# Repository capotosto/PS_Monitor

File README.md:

# Multi-Rail Isolated Power Supply Monitoring System

**Repository:** `PS_Monitor`  
**Author:** Mike Capotosto

## Project Overview

The Multi-Rail Isolated Power Supply Monitoring System measures the voltage and current of up to six floating power-supply rails while preserving galvanic isolation between measurement channels. Each rail is monitored by an LTC2945 power monitor connected through an isolated I²C interface to an Arduino GIGA R1 WiFi. The Arduino firmware performs data acquisition, engineering-unit conversion, alarm evaluation, persistent configuration storage, local display control, HTTP service, and Ethernet communication with an EPICS Input/Output Controller. Measurement and status information is presented locally on the GIGA Display Shield, through a browser-based dashboard, and remotely through a Phoebus Control System Studio operator interface.

The monitored rails are:

- `+5VA`
- `+5VB`
- `+5V`
- `-5V`
- `+15V`
- `-15V`

---

## System Features

- Six isolated voltage and current measurement channels
- LTC2945 voltage, current, and power monitoring
- Independent I²C isolation for each floating rail
- Support for positive and negative supply rails
- Configurable upper and lower voltage limits
- Configurable upper and lower current limits
- Persistent alarm and network settings stored in internal QSPI flash
- Local touchscreen display using the Arduino GIGA Display Shield
- Browser-based monitoring and configuration dashboard
- Ethernet communication through the Arduino Ethernet Shield
- PSC (Portable Streaming Controller) protocol interface for EPICS integration
- EPICS Process Variables for measurements, limits, alarms, and status
- Phoebus OPI for centralized operator monitoring
- I²C communication-error detection
- Text-based alarm states such as `OVL`, `UVL` (over/under voltage limit), `OCL`, and `UCL` (over/under current limit)

---

## System Architecture

### Data Flow

```text
┌──────────────────────────────────────────────┐
│ Floating Power-Supply Rails                  │
│ +5VA, +5VB, +5V, -5V, +15V, and -15V        │
└──────────────────────┬───────────────────────┘
                       │
                       ▼
┌──────────────────────────────────────────────┐
│ LTC2945 Voltage and Current Monitors         │
│ One monitor per power-supply rail            │
└──────────────────────┬───────────────────────┘
                       │
                       ▼
┌──────────────────────────────────────────────┐
│ Isolated I²C Interfaces                      │
│ Maintains isolation between floating rails   │
└──────────────────────┬───────────────────────┘
                       │
                       ▼
┌──────────────────────────────────────────────┐
│ Arduino GIGA R1 WiFi Firmware                │
│                                              │
│ • Sensor acquisition                         │
│ • Engineering-unit conversion                │
│ • Negative-rail sign correction              │
│ • Alarm evaluation                           │
│ • Persistent settings                        │
│ • Local display                              │
│ • HTTP dashboard                             │
│ • PSC protocol server                        │
└───────────────┬────────────────────┬─────────┘
                │                    │
                ▼                    ▼
┌─────────────────────────┐  ┌──────────────────────┐
│ GIGA Display Shield     │  │ Ethernet Network     │
│ Local touchscreen UI    │  │ HTTP and PSC         │
└─────────────────────────┘  └──────────┬───────────┘
                                       │
                                       ▼
                            ┌────────────────────────┐
                            │ EPICS IOC              │
                            │ PSCDriver and records  │
                            └──────────┬─────────────┘
                                       │
                                       ▼
                            ┌────────────────────────┐
                            │ Phoebus / CSS OPI      │
                            │ Operator interface     │
                            └────────────────────────┘
```

### Major Subsystems

| Subsystem | Function |
|---|---|
| Sensor hardware | Measures rail voltage, shunt voltage, current, and power |
| I²C isolation | Preserves galvanic isolation between floating rails |
| Arduino firmware | Acquires data, evaluates alarms, stores settings, and manages communications |
| Local display | Shows rail measurements, limits, alarms, and communication status |
| HTTP dashboard | Provides browser-based monitoring and configuration |
| PSC interface | Transfers measurement and status data to the EPICS IOC |
| EPICS IOC | Converts device data into EPICS Process Variables |
| Phoebus OPI | Provides the centralized operator interface |

---

## Repository Structure

```text
PS_Monitor/
├── README.md
├── hardware/
│   ├── kicad/
│   ├── bom/
│   ├── gerbers/
│   ├── mechanical/
│   └── datasheets/
├── firmware/
│   ├── platformio.ini
│   ├── include/
│   ├── lib/
│   ├── src/
│   └── test/
├── epics-ioc/
│   ├── configure/
│   ├── db/
│   ├── dbd/
│   ├── iocBoot/
│   ├── psuMonitorApp/
│   └── opi/
└── documentation/
```

### Directory Descriptions

- **`/hardware`**  
  KiCad schematic and PCB files, manufacturing outputs, bill of materials, mechanical drawings, and related.

- **`/firmware`**  
  PlatformIO project for the Arduino GIGA R1 WiFi. This directory contains the application source code, configuration headers, local libraries, and build configuration.

- **`/epics-ioc`**  
  EPICS IOC source tree containing database files, record definitions, startup scripts, PSCDriver configuration, device communication settings, and Phoebus Control System Studio displays.

- **`/documentation`**  
  Assorted Documentation

---

## Hardware

### Primary Components

- Arduino GIGA R1 WiFi
- Arduino GIGA Display Shield
- Arduino Ethernet Shield
- LTC2945 voltage, current, and power monitors
- DC1697A LTC2945 demonstration board for prototype testing
- Per-channel I²C digital isolators
- Current-sense shunt resistors
- Custom monitoring and interface PCB
- Six isolated power-supply inputs

### Measurement Method

Each LTC2945 measures:

- Supply voltage
- Differential voltage across a current-sense shunt
- Calculated load current
- Calculated electrical power

Because each monitored supply may float at a different potential, every sensor channel communicates through its own isolated I²C interface. Negative rails are monitored within their isolated domains, and the firmware applies the appropriate sign to the reported engineering values.

---

## Firmware

The firmware is built with PlatformIO using the Arduino Mbed OS framework.

### Main Firmware Modules

| Module | Responsibility |
|---|---|
| `AppState` | Global channel data, settings, alarms, and system state |
| `SensorManager` | Sensor initialization, acquisition, and channel updates |
| `LTC2945` | Low-level LTC2945 register access and unit conversion |
| `DisplayUI` | GIGA Display Shield rendering and status updates |
| `EthernetServices` | Ethernet initialization and network service handling |
| `HttpDashboard` | Browser-based monitoring and configuration |
| `PscProtocol` | PSC protocol communication with the EPICS IOC |
| `PersistentStorage` | QSPI storage of alarm limits and network settings |
| `main` | System initialization and application scheduling |

### Firmware Configuration

Hardware-specific settings are stored in configuration headers, including:

- I²C addresses
- Shunt-resistance values
- Channel names
- Rail polarity
- Voltage and current scaling
- Default alarm limits
- Static network configuration
- MAC address
- PSC port configuration
- Sensor polling intervals

---

## Persistent Settings

The firmware stores configuration data in the Arduino GIGA internal QSPI flash using LittleFS.

Saved settings include:

- Per-channel voltage-low limit
- Per-channel voltage-high limit
- Per-channel current-low limit
- Per-channel current-high limit
- Static IP address
- Subnet mask
- Gateway address
- DNS server address
---

## Network Interfaces

### HTTP Dashboard

The firmware hosts a local web interface for:

- Viewing voltage and current measurements
- Viewing alarm and communication status
- Editing alarm limits
- Editing network parameters
- Saving settings to QSPI

### PSC Protocol

The Arduino exposes a PSC protocol service over Ethernet. The EPICS IOC connects to the device using PSCDriver and maps transmitted parameters into EPICS records.

---

## EPICS IOC

### Requirements

- EPICS Base
- ASYN
- PSCDriver
- A supported Linux environment
- Phoebus for the operator interface

### Build the IOC

From the repository root:

```bash
cd epics-ioc
make
```

### Start the IOC

```bash
cd iocBoot/iocpsuMonitor
./st.cmd
```

An equivalent direct launch command may also be used:

```bash
../../bin/linux-x86_64/psuMonitor st.cmd
```

### Example IOC Configuration

```text
P=TEST:
R=GIGA
DEVICE=GIGA_PSC
HOST=192.168.1.177
PORT=8765
```

The final values are defined in the IOC startup script.

---

## EPICS Process Variables

The IOC is intended to provide Process Variables for:

- Channel voltage
- Channel current
- Voltage-low limit
- Voltage-high limit
- Current-low limit
- Current-high limit
- Voltage alarm status
- Current alarm status
- Sensor communication status
- I²C error status
- Arduino connection status
- Network information
- Firmware status

### Alarm States

| Status | Meaning |
|---|---|
| `OK` | Measurement is within configured limits |
| `OVL` | Over-voltage limit |
| `UVL` | Under-voltage limit |
| `OCL` | Over-current limit |
| `UCL` | Under-current limit |
| `I2C Error` | Sensor communication failure |
| `Disconnected` | IOC communication failure |

---

## Operator Interface

The Phoebus OPI provides a centralized display for all monitored rails.

Planned or implemented interface elements include:

- Voltage and current readbacks
- Alarm-limit displays
- Text-based alarm indicators
- Connection-status indicator
- I²C error indicator
- Per-channel status cards
- Network and firmware information
- Overall system status

---

## Project Milestones

- [x] Define system requirements and monitored power rails
- [x] Select the Arduino GIGA R1 WiFi as the primary controller
- [x] Establish the PlatformIO firmware project
- [x] Develop the initial six-channel display layout
- [x] Add configurable voltage and current alarm limits
- [x] Establish the Ethernet and PSC communication architecture
- [x] Complete single-channel LTC2945 prototype validation
- [ ] Verify current scaling for each shunt-resistor value
- [ ] Complete six-channel isolated I²C hardware
- [ ] Finalize persistent storage and recovery testing
- [ ] Complete browser-based configuration testing
- [ ] Finalize EPICS database records
- [ ] Complete Phoebus OPI
- [ ] Fabricate and assemble the custom PCB
- [ ] Calibrate all measurement channels
- [ ] Perform end-to-end system validation
- [ ] Complete final project documentation

---

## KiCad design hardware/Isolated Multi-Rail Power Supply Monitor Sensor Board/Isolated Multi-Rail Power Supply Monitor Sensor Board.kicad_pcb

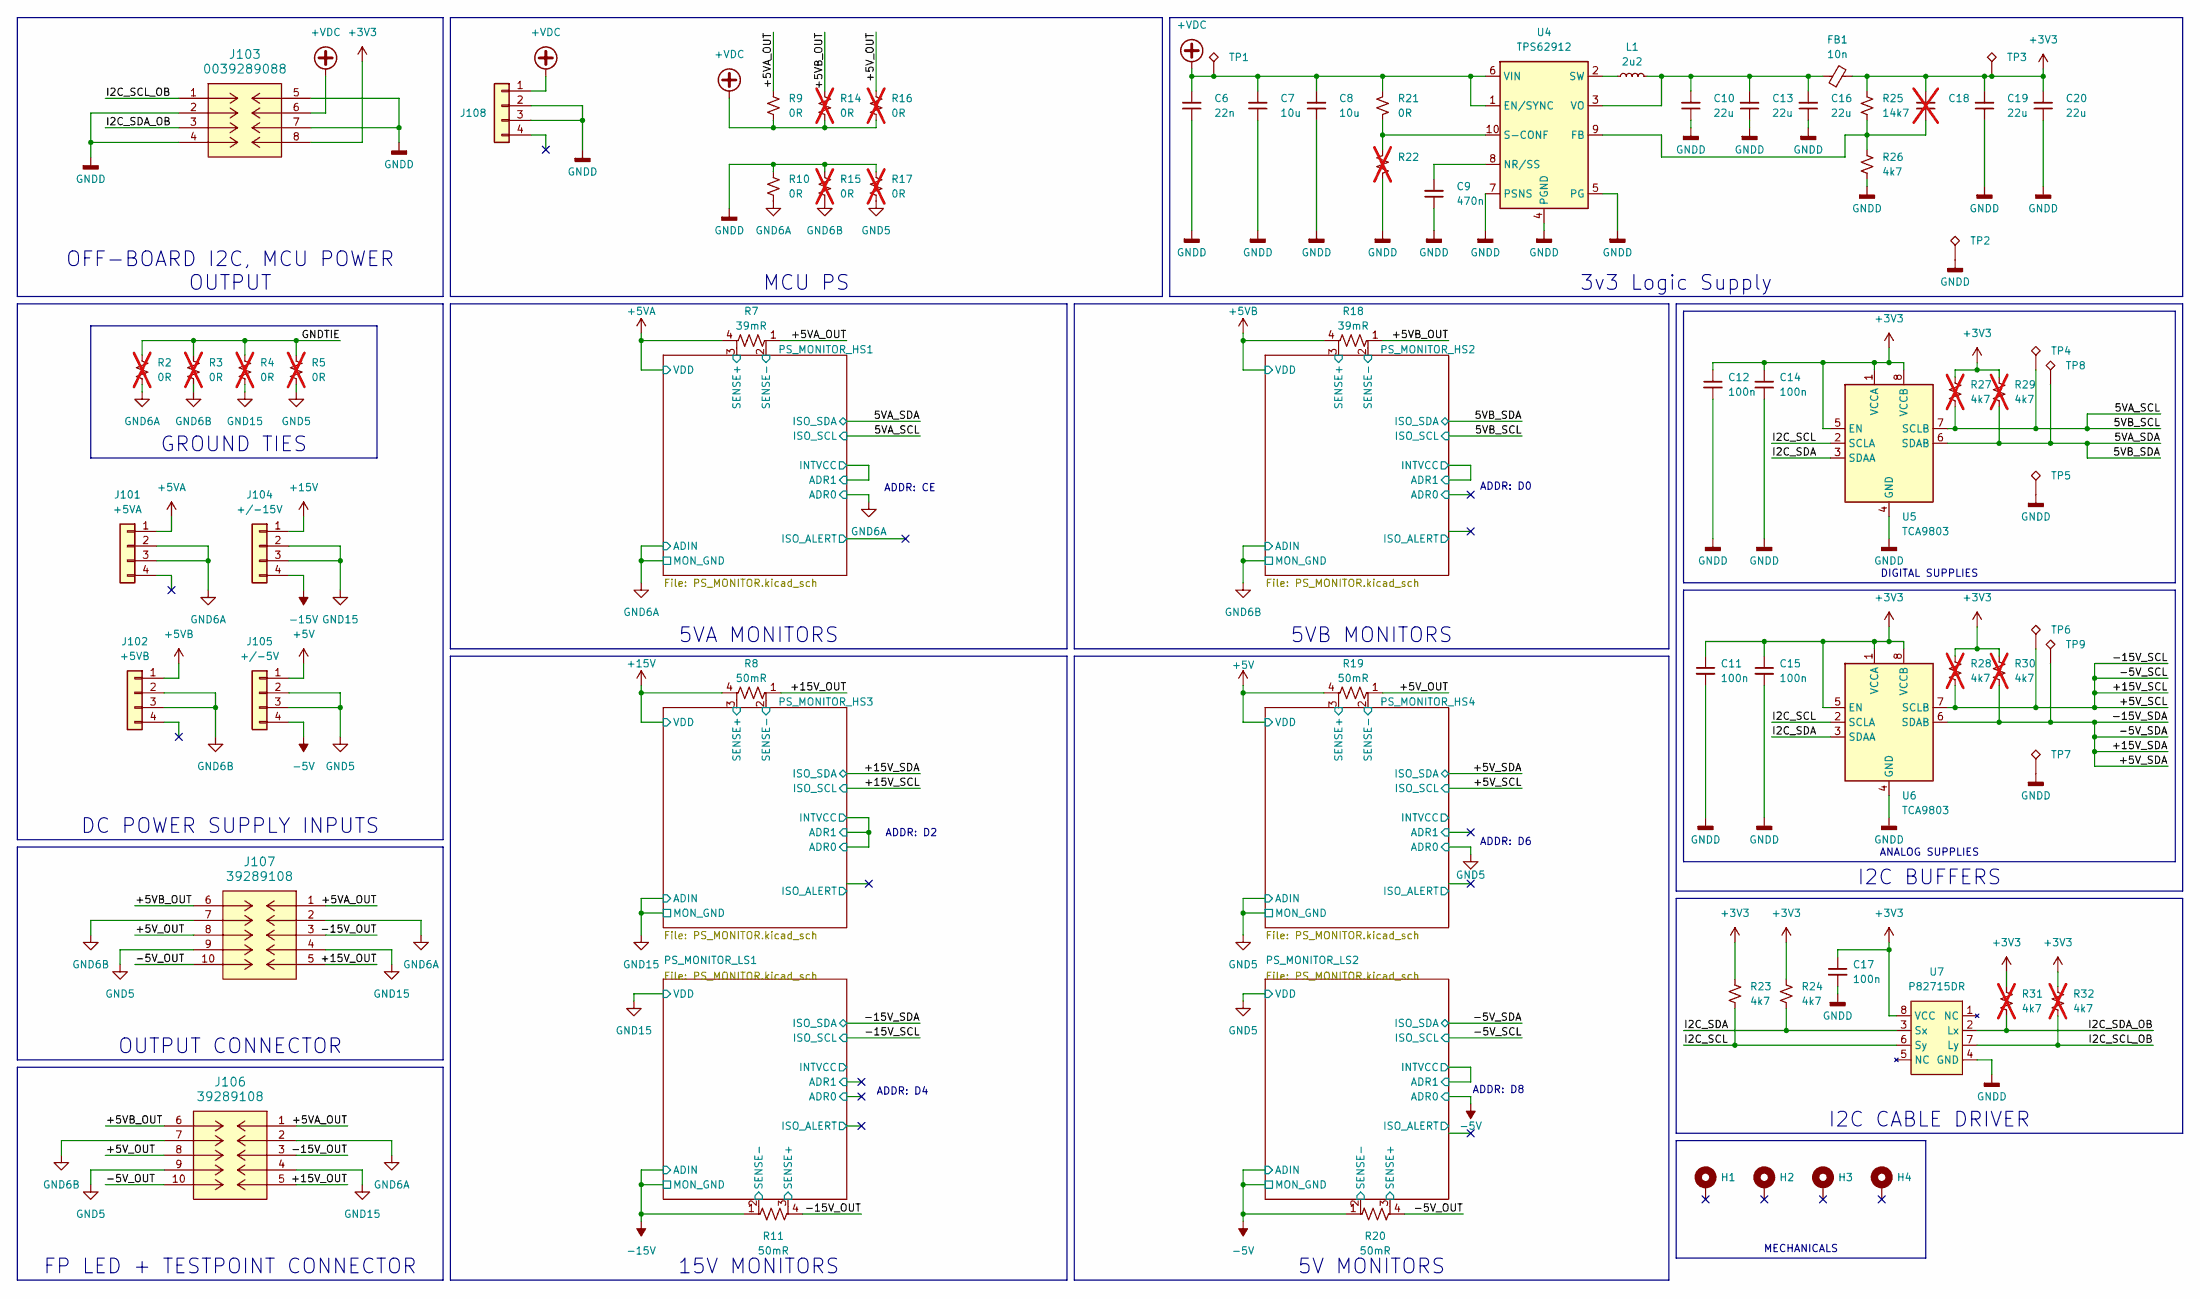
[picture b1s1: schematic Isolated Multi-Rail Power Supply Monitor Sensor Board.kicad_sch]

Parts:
C6: 22n; C_0402_1005Metric; MPN GRM155R71H222KA01D
C7, C8: 10u; C_0805_2012Metric; MPN C2012X7S1E106K125AC
C9: 470n; C_0402_1005Metric; MPN C1005X5R1E474K050BB
C10, C13, C16, C19, C20: 22u; C_0805_2012Metric; MPN GMC21X7S226M10NT
C11, C12, C14, C15, C17: 100n; C_0402_1005Metric; MPN GRM155R61H104KE14D
C18: C_0603_1608Metric; not fitted
FB1: 10n; L_0603_1608Metric; MPN BLE18PS080SN1D
H1, H2, H3, H4: MountingHole_Pad; MountingHole_3.2mm_M3_DIN965_Pad
J101: +5VA; Molex_Mini-Fit_Jr_5566-04A2_2x02_P4.20mm_Vertical; MPN 0039299049
J102: +5VB; Molex_Mini-Fit_Jr_5566-04A2_2x02_P4.20mm_Vertical; MPN 0039299049
J103: 0039289088; Molex_Mini-Fit_Jr_5566-08A2_2x04_P4.20mm_Vertical; MPN 0039289088
J104: +/-15V; Molex_Mini-Fit_Jr_5566-04A2_2x02_P4.20mm_Vertical; MPN 0039299049
J105: +/-5V; Molex_Mini-Fit_Jr_5566-04A2_2x02_P4.20mm_Vertical; MPN 0039299049
J106, J107: 39289108; Molex_Mini-Fit_Jr_5566-10A2_2x05_P4.20mm_Vertical; MPN 0039289108
J108: Conn_01x04; Molex_Mini-Fit_Jr_5566-04A2_2x02_P4.20mm_Vertical; MPN 0039299049
L1: 2u2; 74438356022; MPN 74438356022
R2, R3, R4, R5, R14, R15, R16, R17: 0R; R_1206_3216Metric; Tolerance JUMPER; MPN 5108; not fitted
R7, R18: 39mR; R_Shunt_Ohmite_LVK20; MPN LVK20R039FER
R8, R11, R19, R20: 50mR; R_Shunt_Ohmite_LVK20; MPN LVK20R050FER
R9, R10: 0R; R_1206_3216Metric; Tolerance JUMPER; MPN 5108
R21: 0R; R_0402_1005Metric; MPN CRCW04020000Z0ED
R22: R_0402_1005Metric; not fitted
R23, R24: 4k7; R_0402_1005Metric; MPN CRCW04024K70FKED
R25: 14k7; R_0402_1005Metric; MPN ERA-2APB1472X
R26: 4k7; R_0402_1005Metric; MPN ERA-2ARB472X
R27, R28, R29, R30, R31, R32: 4k7; R_0402_1005Metric; MPN CRCW04024K70FKED; not fitted
TP1, TP3: 5000; TestPoint_Keystone_5000-5004_Miniature; MPN 5000
TP2: 5001; TestPoint_Keystone_5000-5004_Miniature; MPN 5001
TP4, TP5, TP6, TP7, TP8, TP9: 5015; TestPoint_Keystone_5015_Micro_Mini; MPN 5015
U4: TPS62912; Texas_RPU0010A_VQFN-HR-10_2x2mm_P0.5mm; MPN TPS62912RPUR
U5, U6: TCA9803; VSSOP-8_3x3mm_P0.65mm; MPN TCA9803DGKR
U7: P82715DR; SOIC-8_3.9x4.9mm_P1.27mm; MPN P82B715DR

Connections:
+3V3: C11.1, C12.1, C14.1, C15.1, C17.1, C18.2, C19.2, C20.2, FB1.2, J103.8, R23.2, R24.2, R25.1, R27.2, R28.2, R29.2, R30.2, R31.2, R32.2, TP3.1, U5.1 (VCCA), U5.5 (EN), U5.8 (VCCB), U6.1 (VCCA), U6.5 (EN), U6.8 (VCCB), U7.8 (VCC); also elsewhere on the board
+5V: J105.1, R19.4; also elsewhere on the board
+6VA: J101.1, R7.4; also elsewhere on the board
+6VB: J102.1, R18.4; also elsewhere on the board
+15V: J104.1, R8.4; also elsewhere on the board
+VDC: C6.2, C7.2, C8.2, J103.6, J108.1, R9.2, R14.2, R16.2, R21.1, TP1.1, U4.1 (EN/SYNC), U4.6 (VIN)
-5V: J105.4, R20.1; also elsewhere on the board
-15V: J104.4, R11.1; also elsewhere on the board
/6VA_SCL: R27.1, TP4.1, U5.7 (SCLB); also elsewhere on the board
/6VA_SDA: R29.1, TP8.1, U5.6 (SDAB); also elsewhere on the board
/+5V_OUT: J106.8, J107.8, R16.1, R19.1
/+6VA_OUT: J106.1, J107.1, R7.1, R9.1
/+6VB_OUT: J106.6, J107.6, R14.1, R18.1
/+15V_OUT: J106.5, J107.5, R8.1
/+15V_SCL: R28.1, TP6.1, U6.7 (SCLB); also elsewhere on the board
/+15V_SDA: R30.1, TP9.1, U6.6 (SDAB); also elsewhere on the board
/-5V_OUT: J106.10, J107.10, R20.4
/-15V_OUT: J106.3, J107.3, R11.4
/GNDTIE: R2.1, R3.1, R4.1, R5.1
/I2C_SCL: R23.1, U5.2 (SCLA), U6.2 (SCLA), U7.6 (Sy)
/I2C_SCL_OB: J103.1, R32.1, U7.7 (Ly)
/I2C_SDA: R24.1, U5.3 (SDAA), U6.3 (SDAA), U7.3 (Sx)
/I2C_SDA_OB: J103.3, R31.1, U7.2 (Lx)
/PS_MONITOR_HS1/SENSE+: R7.3; also elsewhere on the board
/PS_MONITOR_HS1/SENSE-: R7.2; also elsewhere on the board
/PS_MONITOR_HS2/SENSE+: R18.3; also elsewhere on the board
/PS_MONITOR_HS2/SENSE-: R18.2; also elsewhere on the board
/PS_MONITOR_HS3/SENSE+: R8.3; also elsewhere on the board
/PS_MONITOR_HS3/SENSE-: R8.2; also elsewhere on the board
/PS_MONITOR_HS4/SENSE+: R19.3; also elsewhere on the board
/PS_MONITOR_HS4/SENSE-: R19.2; also elsewhere on the board
/PS_MONITOR_LS1/SENSE+: R11.3; also elsewhere on the board
/PS_MONITOR_LS1/SENSE-: R11.2; also elsewhere on the board
/PS_MONITOR_LS2/SENSE+: R20.3; also elsewhere on the board
/PS_MONITOR_LS2/SENSE-: R20.2; also elsewhere on the board
GND5: J105.2, J105.3, J106.9, J107.9, R5.2, R17.2; also elsewhere on the board
GND6A: J101.2, J101.3, J106.2, J107.2, R2.2, R10.2; also elsewhere on the board
GND6B: J102.2, J102.3, J106.7, J107.7, R3.2, R15.2; also elsewhere on the board
GND15: J104.2, J104.3, J106.4, J107.4, R4.2; also elsewhere on the board
GNDD: C6.1, C7.1, C8.1, C9.1, C10.1, C11.2, C12.2, C13.1, C14.2, C15.2, C16.1, C17.2, C19.1, C20.1, J103.2, J103.4, J103.5, J103.7, J108.2, J108.3, R10.1, R15.1, R17.1, R22.2, R26.2, TP2.1, TP5.1, TP7.1, U4.4 (PGND), U4.5 (PG), U4.7 (PSNS), U5.4 (GND), U6.4 (GND), U7.4 (GND); also elsewhere on the board
unnamed: C18.1, R25.2, R26.1, U4.9 (FB)
unnamed: C9.2, U4.8 (NR/SS)
unnamed: R21.2, R22.1, U4.10 (S-CONF)
unnamed: L1.1, U4.2 (SW)
unnamed: C10.2, C13.2, C16.2, FB1.1, L1.2, U4.3 (VO)

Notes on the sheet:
ADDR: D0
ADDR: D6
ADDR: D2
ADDR: D4
ADDR: D8
ADDR: CE
I2C BUFFERS
ANALOG SUPPLIES
5V MONITORS
5VA MONITORS
OFF-BOARD I2C, MCU POWER OUTPUT
3v3 Logic Supply
GROUND TIES
I2C CABLE DRIVER
5VB MONITORS
15V MONITORS
MECHANICALS
FP LED + TESTPOINT CONNECTOR
OUTPUT CONNECTOR
MCU PS
DC POWER SUPPLY INPUTS
DIGITAL SUPPLIES

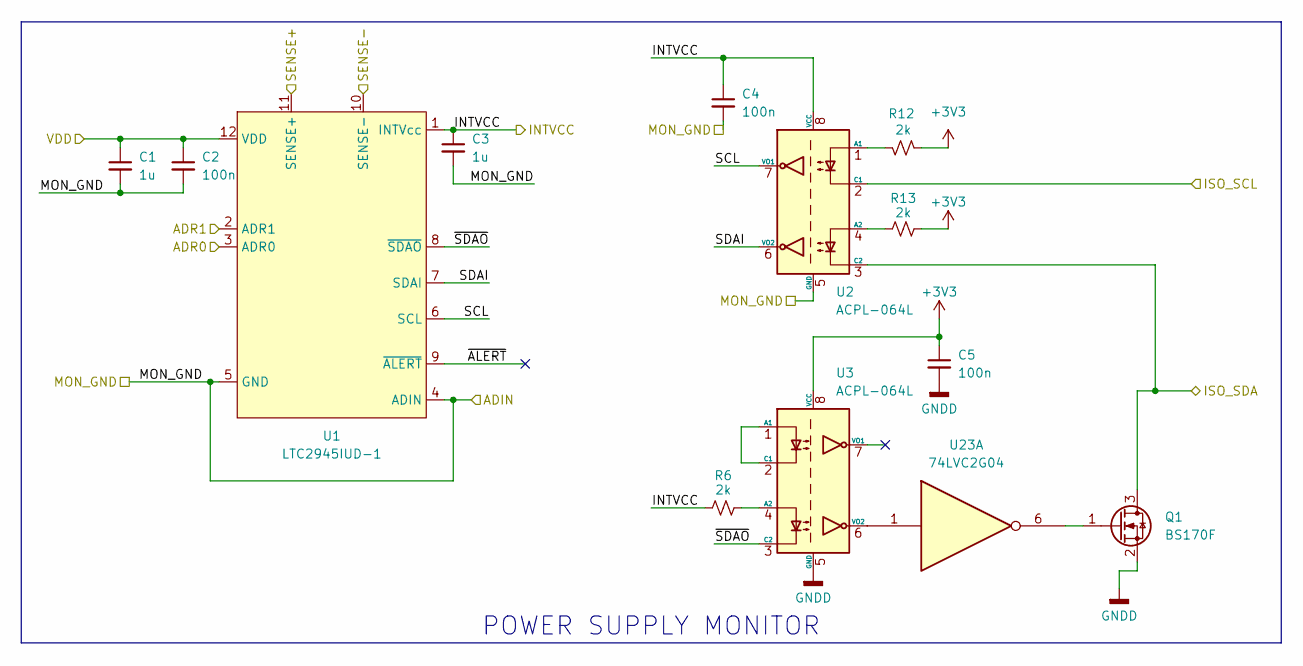
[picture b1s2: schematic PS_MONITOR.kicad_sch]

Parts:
C1, C3: 1u; C_0603_1608Metric; MPN CL10A105KB8NNNC
C2, C4, C5: 100n; C_0402_1005Metric; MPN GRM155R61H104KE14D
Q1: BS170F; SOT-416; MPN NTA7002NT1G
R6, R12, R13: 2k; R_0402_1005Metric; MPN ERJ-2RKF2001X
U1: LTC2945IUD-1; QFN-12-1EP_3x3mm_P0.5mm_EP1.65x1.65mm_ThermalVias; MPN LTC2945IUD#TRPBF
U2, U3: ACPL-064L; SOIC-8_3.9x4.9mm_P1.27mm; MPN ACPL-064L-500E
U23: 74LVC2G04

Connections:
+3V3: C5.1, R12.1, R13.2, U3.8 (VCC); also elsewhere on the board
+6VA: C1.1, C2.1, U1.12 (VDD); also elsewhere on the board
/6VA_SCL: U2.2 (C1); also elsewhere on the board
/6VA_SDA: Q1.3 (D), U2.3 (C2); also elsewhere on the board
/PS_MONITOR_HS1/INTVCC: C3.1, C4.1, R6.1, U1.1 (INTVcc), U1.2 (ADR1), U2.8 (VCC)
/PS_MONITOR_HS1/SCL: U1.6 (SCL), U2.7 (VO1)
/PS_MONITOR_HS1/SDAI: U1.7 (SDAI), U2.6 (VO2)
/PS_MONITOR_HS1/SENSE+: U1.11 (SENSE+); also elsewhere on the board
/PS_MONITOR_HS1/SENSE-: U1.10 (SENSE-); also elsewhere on the board
/PS_MONITOR_HS1/~ALERT: U1.9 (~ALERT)
/PS_MONITOR_HS1/~SDAO: U1.8 (~SDAO), U3.3 (C2)
GND6A: C1.2, C2.2, C3.2, C4.2, U1.3 (ADR0), U1.4 (ADIN), U1.5 (GND), U1.13 (GND), U2.5 (GND); also elsewhere on the board
GNDD: C5.2, Q1.2 (S), U3.5 (GND); also elsewhere on the board
unnamed: Q1.1 (G), U3.6 (VO2)
unnamed: R12.2, U2.1 (A1)
unnamed: R13.1, U2.4 (A2)
unnamed: U3.1 (A1), U3.2 (C1)
unnamed: R6.2, U3.4 (A2)

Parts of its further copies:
C21, C23, C26, C28, C31, C33, C36, C38, C41, C43: 1u; C_0603_1608Metric; MPN CL10A105KB8NNNC
C22, C24, C25, C27, C29, C30, C32, C34, C35, C37, C39, C40, C42, C44, C45: 100n; C_0402_1005Metric; MPN GRM155R61H104KE14D
Q2, Q3, Q4, Q5, Q6: BS170F; SOT-416; MPN NTA7002NT1G
R33, R34, R35, R36, R37, R38, R39, R40, R41, R42, R43, R44, R45, R46, R47: 2k; R_0402_1005Metric; MPN ERJ-2RKF2001X
U8, U11, U14, U17, U20: LTC2945IUD-1; QFN-12-1EP_3x3mm_P0.5mm_EP1.65x1.65mm_ThermalVias; MPN LTC2945IUD#TRPBF
U9, U10, U12, U13, U15, U16, U18, U19, U21, U22: ACPL-064L; SOIC-8_3.9x4.9mm_P1.27mm; MPN ACPL-064L-500E

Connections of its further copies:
+3V3: C25.1, C30.1, C35.1, C40.1, C45.1, R34.1, R35.2, R37.1, R38.2, R40.1, R41.2, R43.1, R44.2, R46.1, R47.2, U10.8 (VCC), U13.8 (VCC), U16.8 (VCC), U19.8 (VCC), U22.8 (VCC); also elsewhere on the board
+5V: C31.1, C32.1, U14.12 (VDD); also elsewhere on the board
+6VB: C21.1, C22.1, U8.12 (VDD); also elsewhere on the board
+15V: C26.1, C27.1, U11.12 (VDD); also elsewhere on the board
-5V: C41.2, C42.2, C43.2, C44.2, U20.3 (ADR0), U20.4 (ADIN), U20.5 (GND), U20.13 (GND), U21.5 (GND); also elsewhere on the board
-15V: C36.2, C37.2, C38.2, C39.2, U17.4 (ADIN), U17.5 (GND), U17.13 (GND), U18.5 (GND); also elsewhere on the board
/6VA_SCL: U9.2 (C1); also elsewhere on the board
/6VA_SDA: Q2.3 (D), U9.3 (C2); also elsewhere on the board
/+15V_SCL: U12.2 (C1), U15.2 (C1), U18.2 (C1), U21.2 (C1); also elsewhere on the board
/+15V_SDA: Q3.3 (D), Q4.3 (D), Q5.3 (D), Q6.3 (D), U12.3 (C2), U15.3 (C2), U18.3 (C2), U21.3 (C2); also elsewhere on the board
/PS_MONITOR_HS2/ADR0: U8.3 (ADR0)
/PS_MONITOR_HS2/INTVCC: C23.1, C24.1, R33.1, U8.1 (INTVcc), U8.2 (ADR1), U9.8 (VCC)
/PS_MONITOR_HS2/SCL: U8.6 (SCL), U9.7 (VO1)
/PS_MONITOR_HS2/SDAI: U8.7 (SDAI), U9.6 (VO2)
/PS_MONITOR_HS2/SENSE+: U8.11 (SENSE+); also elsewhere on the board
/PS_MONITOR_HS2/SENSE-: U8.10 (SENSE-); also elsewhere on the board
/PS_MONITOR_HS2/~ALERT: U8.9 (~ALERT)
/PS_MONITOR_HS2/~SDAO: U8.8 (~SDAO), U10.3 (C2)
/PS_MONITOR_HS3/INTVCC: C28.1, C29.1, R36.1, U11.1 (INTVcc), U11.2 (ADR1), U11.3 (ADR0), U12.8 (VCC)
/PS_MONITOR_HS3/SCL: U11.6 (SCL), U12.7 (VO1)
/PS_MONITOR_HS3/SDAI: U11.7 (SDAI), U12.6 (VO2)
/PS_MONITOR_HS3/SENSE+: U11.11 (SENSE+); also elsewhere on the board
/PS_MONITOR_HS3/SENSE-: U11.10 (SENSE-); also elsewhere on the board
/PS_MONITOR_HS3/~ALERT: U11.9 (~ALERT)
/PS_MONITOR_HS3/~SDAO: U11.8 (~SDAO), U13.3 (C2)
/PS_MONITOR_HS4/ADR1: U14.2 (ADR1)
/PS_MONITOR_HS4/INTVCC: C33.1, C34.1, R39.1, U14.1 (INTVcc), U15.8 (VCC)
/PS_MONITOR_HS4/SCL: U14.6 (SCL), U15.7 (VO1)
/PS_MONITOR_HS4/SDAI: U14.7 (SDAI), U15.6 (VO2)
/PS_MONITOR_HS4/SENSE+: U14.11 (SENSE+); also elsewhere on the board
/PS_MONITOR_HS4/SENSE-: U14.10 (SENSE-); also elsewhere on the board
/PS_MONITOR_HS4/~ALERT: U14.9 (~ALERT)
/PS_MONITOR_HS4/~SDAO: U14.8 (~SDAO), U16.3 (C2)
/PS_MONITOR_LS1/ADR0: U17.3 (ADR0)
/PS_MONITOR_LS1/ADR1: U17.2 (ADR1)
/PS_MONITOR_LS1/INTVCC: C38.1, C39.1, R42.1, U17.1 (INTVcc), U18.8 (VCC)
/PS_MONITOR_LS1/SCL: U17.6 (SCL), U18.7 (VO1)
/PS_MONITOR_LS1/SDAI: U17.7 (SDAI), U18.6 (VO2)
/PS_MONITOR_LS1/SENSE+: U17.11 (SENSE+); also elsewhere on the board
/PS_MONITOR_LS1/SENSE-: U17.10 (SENSE-); also elsewhere on the board
/PS_MONITOR_LS1/~ALERT: U17.9 (~ALERT)
/PS_MONITOR_LS1/~SDAO: U17.8 (~SDAO), U19.3 (C2)
/PS_MONITOR_LS2/INTVCC: C43.1, C44.1, R45.1, U20.1 (INTVcc), U20.2 (ADR1), U21.8 (VCC)
/PS_MONITOR_LS2/SCL: U20.6 (SCL), U21.7 (VO1)
/PS_MONITOR_LS2/SDAI: U20.7 (SDAI), U21.6 (VO2)
/PS_MONITOR_LS2/SENSE+: U20.11 (SENSE+); also elsewhere on the board
/PS_MONITOR_LS2/SENSE-: U20.10 (SENSE-); also elsewhere on the board
/PS_MONITOR_LS2/~ALERT: U20.9 (~ALERT)
/PS_MONITOR_LS2/~SDAO: U20.8 (~SDAO), U22.3 (C2)
GND5: C31.2, C32.2, C33.2, C34.2, C41.1, C42.1, U14.3 (ADR0), U14.4 (ADIN), U14.5 (GND), U14.13 (GND), U15.5 (GND), U20.12 (VDD); also elsewhere on the board
GND6B: C21.2, C22.2, C23.2, C24.2, U8.4 (ADIN), U8.5 (GND), U8.13 (GND), U9.5 (GND); also elsewhere on the board
GND15: C26.2, C27.2, C28.2, C29.2, C36.1, C37.1, U11.4 (ADIN), U11.5 (GND), U11.13 (GND), U12.5 (GND), U17.12 (VDD); also elsewhere on the board
GNDD: C25.2, C30.2, C35.2, C40.2, C45.2, Q2.2 (S), Q3.2 (S), Q4.2 (S), Q5.2 (S), Q6.2 (S), U10.5 (GND), U13.5 (GND), U16.5 (GND), U19.5 (GND), U22.5 (GND); also elsewhere on the board
unnamed: Q2.1 (G), U10.6 (VO2)
unnamed: Q3.1 (G), U13.6 (VO2)
unnamed: Q4.1 (G), U16.6 (VO2)
unnamed: Q5.1 (G), U19.6 (VO2)
unnamed: Q6.1 (G), U22.6 (VO2)
unnamed: R34.2, U9.1 (A1)
unnamed: R35.1, U9.4 (A2)
unnamed: U10.1 (A1), U10.2 (C1)
unnamed: R33.2, U10.4 (A2)
unnamed: R37.2, U12.1 (A1)
unnamed: R38.1, U12.4 (A2)
unnamed: U13.1 (A1), U13.2 (C1)
unnamed: R36.2, U13.4 (A2)
unnamed: R40.2, U15.1 (A1)
unnamed: R41.1, U15.4 (A2)
unnamed: U16.1 (A1), U16.2 (C1)
unnamed: R39.2, U16.4 (A2)
unnamed: R43.2, U18.1 (A1)
unnamed: R44.1, U18.4 (A2)
unnamed: U19.1 (A1), U19.2 (C1)
unnamed: R42.2, U19.4 (A2)
unnamed: R46.2, U21.1 (A1)
unnamed: R47.1, U21.4 (A2)
unnamed: U22.1 (A1), U22.2 (C1)
unnamed: R45.2, U22.4 (A2)

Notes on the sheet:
POWER SUPPLY MONITOR

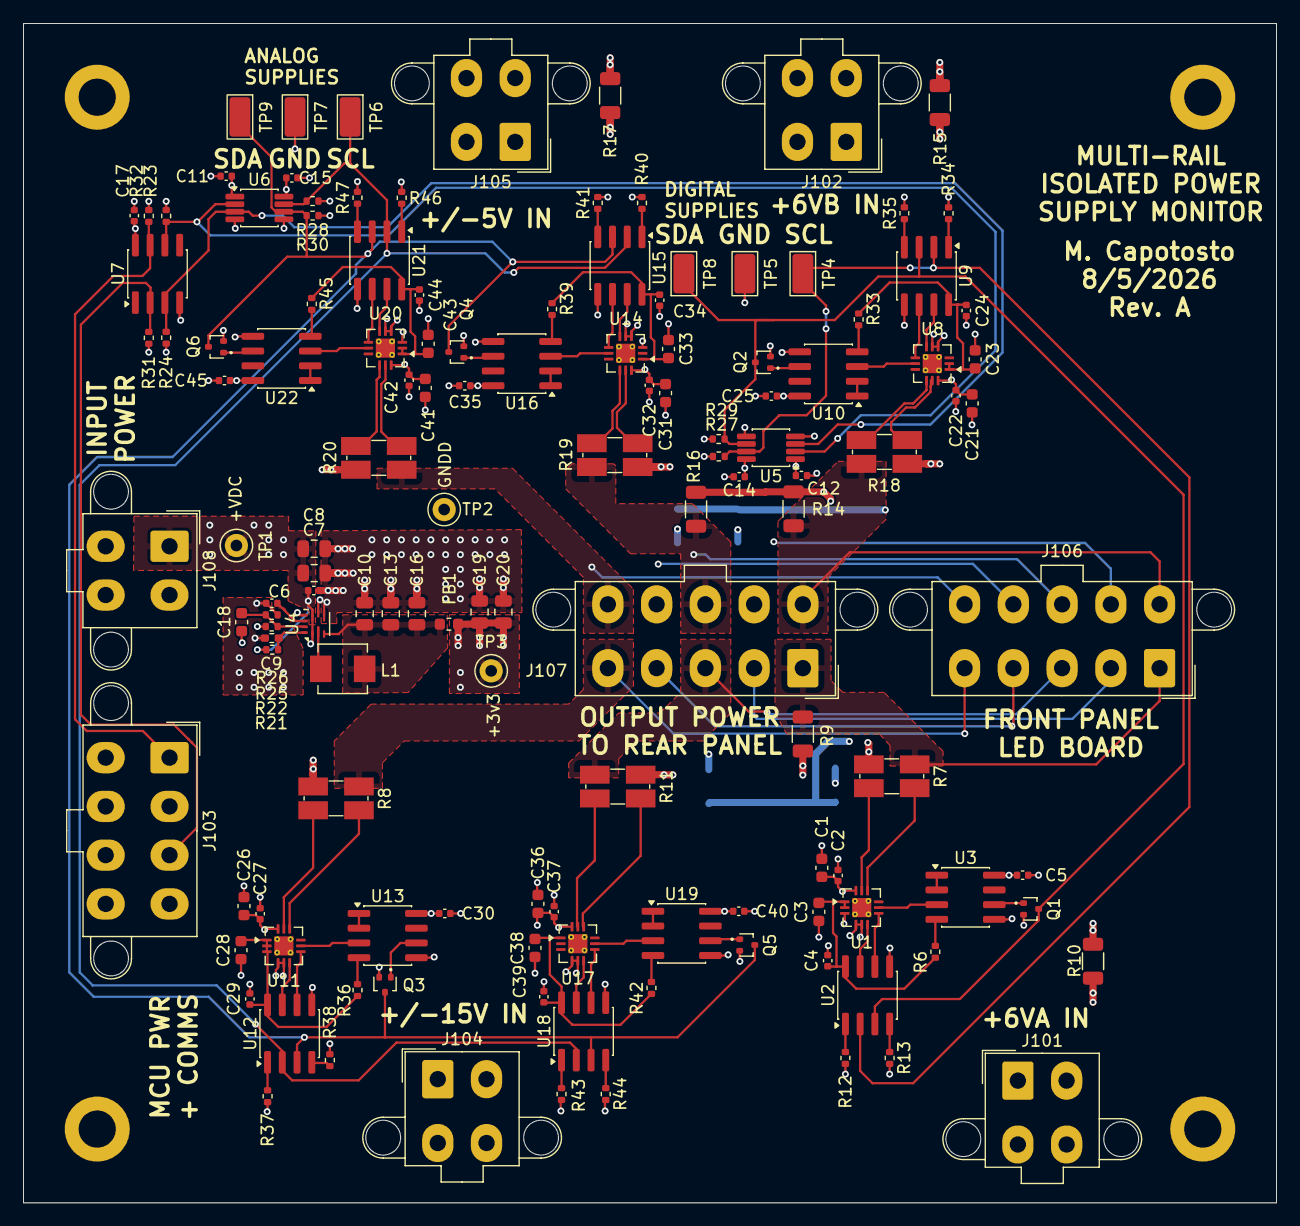
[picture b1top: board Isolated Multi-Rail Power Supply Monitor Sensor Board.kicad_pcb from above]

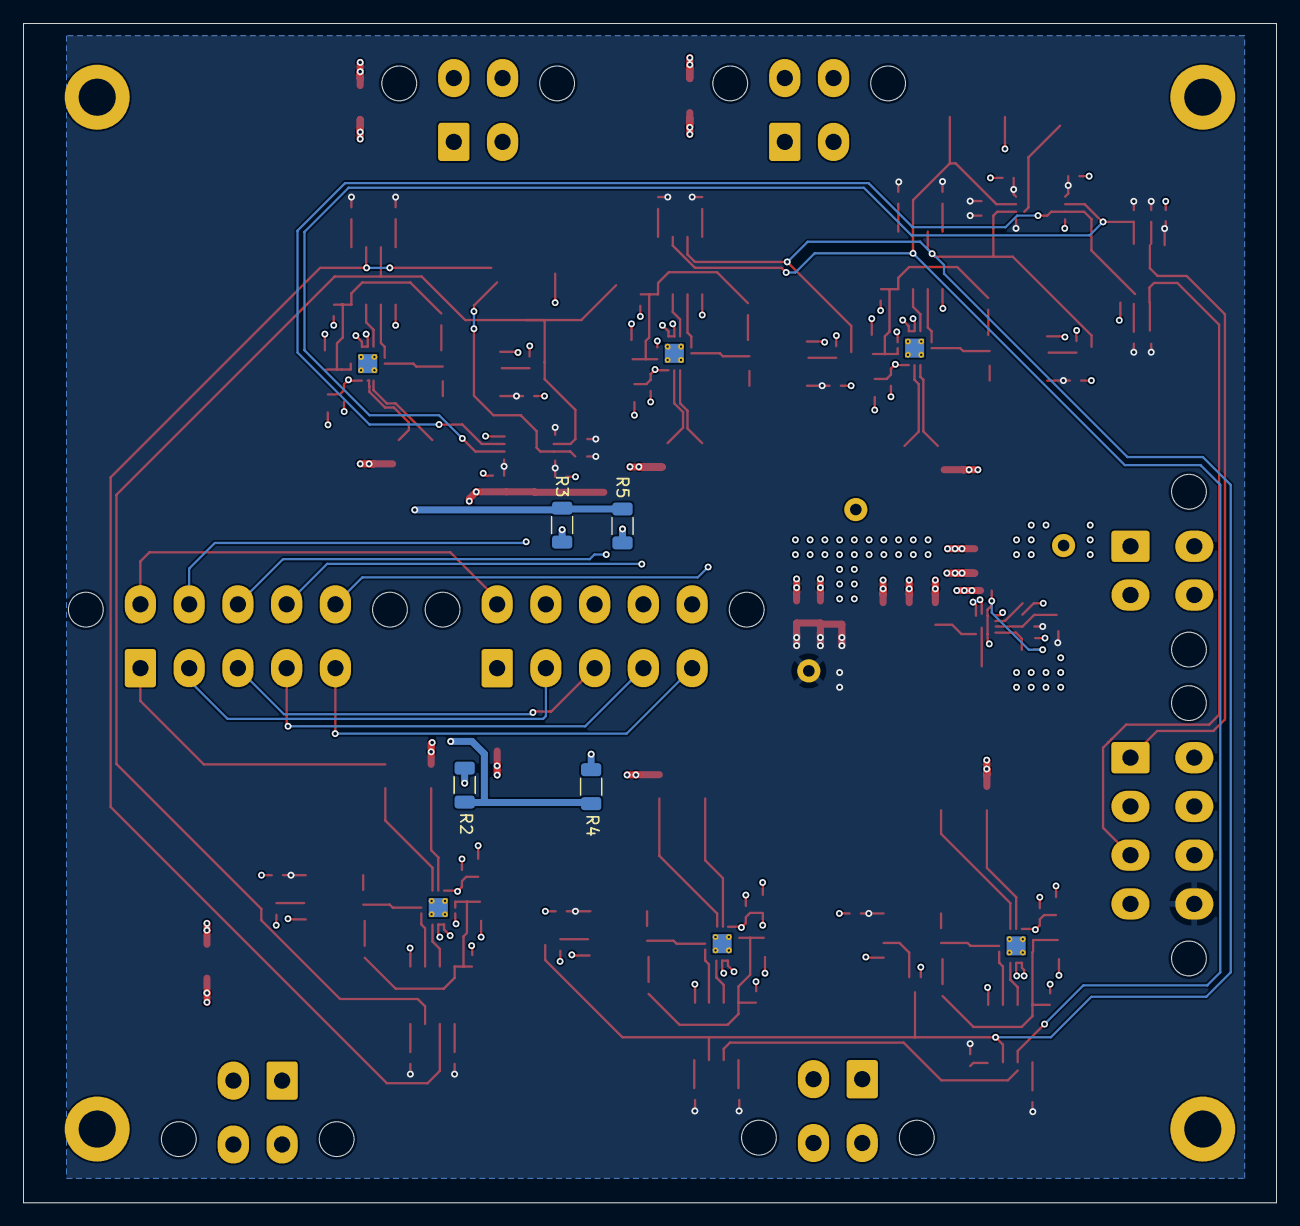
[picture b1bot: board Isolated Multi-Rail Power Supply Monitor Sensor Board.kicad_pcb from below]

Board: 6 copper layers, 108.0 x 101.6 mm, 142 parts (4 on the bottom side), 99 nets.

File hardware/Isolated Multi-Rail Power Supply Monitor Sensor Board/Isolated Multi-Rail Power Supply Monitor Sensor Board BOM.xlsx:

BOM: Power Sensor Board |  | Production Quantity: | 1 | Tape and Reel/Reeling Fees Allowable? | No | Add 10% spares for components excluding modules
Reference | Value | DNP | MPN | Manufacturer | DPN | Distributor | Qty | Qty+10% | Order Qty | Extended Price
C1,C3,C21,C23,C26,C28,C31,C33,C36,C38,C41,C43 | 1u |  | CL10A105KB8NNNC | Samsung Electro-Mechanics | 1276-1860-6-ND | Digikey | 12 | 14 | 100 | 3.77
C2,C4,C5,C11,C12,C14,C15,C17,C22,C24,C25,C27,C29,C30,C32,C34,C35,C37,C39,C40,C4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 | 100n |  | GRM155R61H104KE14D | Murata Electronics | 490-10697-6-ND | Digikey | 23 | 26 | 100 | 1.41
C6 | 22n |  | GRM155R71H222KA01D | Murata Electronics | 490-1305-6-ND | Digikey | 1 | 2 | 100 | 1.01
C7,C8 | 10u |  | C2012X7S1E106K125AC | TDK | 445-181600-6-ND | Digikey | 2 | 3 | 10 | 3.58
C9 | 470n |  | C1005X5R1E474K050BB | TDK | 445-8020-6-ND | Digikey | 1 | 2 | 100 | 3.17
C10,C13,C16,C19,C20 | 22u |  | GMC21X7S226M10NT | Cal-Chip Electronics, Inc. | 4713-GMC21X7S226M10NTDKR-ND | Digikey | 5 | 6 | 15 | 11.295
C18 | ~ | DNP |  |  |  |  | 1 | 2
FB1 | 10n |  | BLE18PS080SN1D | Murata Electronics | 490-BLE18PS080SN1DDKR-ND | Digikey | 1 | 2 | 10 | 2.2999999999999998
H1,H2,H3,H4 | MountingHole_Pad |  |  |  |  |  | 4 | 5
J101 | +6VA |  | 0039299049 | Molex | WM14518-ND | Digikey | 1 | 2 | 1 | 2.7
J102 | +6VB |  | 0039299049 | Molex | WM14518-ND | Digikey | 1 | 2 | 1 | 2.7
J103 | 0039289088 |  | 0039289088 | Molex | WM3835-ND | Digikey | 1 | 2 | 1 | 4.58
J104 | +/-15V |  | 0039299049 | Molex | WM14518-ND | Digikey | 1 | 2 | 1 | 2.7
J105 | +/-5V |  | 0039299049 | Molex | WM14518-ND | Digikey | 1 | 2 | 1 | 2.7
J106,J107 | 39289108 |  | 0039289108 | Molex | 23-0039289108-ND | Digikey | 2 | 3 | 1 | 5.0199999999999996
J108 | Conn_01x04 |  | 0039299049 | Molex | WM14518-ND | Digikey | 1 | 2 | 1 | 2.7
L1 | 2u2 |  | 74438356022 | Wurth Elektronik | 732-8232-6-ND | Digikey | 1 | 2 | 3 | 5.82
Q1,Q2,Q3,Q4,Q5,Q6 | BS170F |  | NTA7002NT1G | onsemi | NTA7002NT1GOSDKR-ND | Digikey | 6 | 7 | 25 | 4.4249999999999998
R2,R3,R4,R5,R14,R15,R16,R17 | 0R | DNP | 5108 | Keystone Electronics | 36-5108DKR-ND | Digikey | 8 | 9
R6,R12,R13,R33,R34,R35,R36,R37,R38,R39,R40,R41,R42,R43,R44,R45,R46,R47 | 2k |  | ERJ-2RKF2001X | Panasonic Industry | P2.00KLDKR-ND | Digikey | 18 | 20 | 100 | 1.64
R7,R18 | 39mR |  | LVK20R039FER | Ohmite | 273-LVK20R039FERDKR-ND | Ohmite | 2 | 3 | 5 | 9.4499999999999993
R8,R11,R19,R20 | 50mR |  | LVK20R050FER | Ohmite | 273-LVK20R050FERDKR-ND | Ohmite | 4 | 5 | 5 | 9.4499999999999993
R9,R10 | 0R |  | 5108 | Keystone Electronics | 36-5108DKR-ND | Digikey | 2 | 3 | 10 | 2.0099999999999998
R21 | 0R |  | CRCW04020000Z0ED | Vishay Dale | 541-0.0JDKR-ND | Digikey | 1 | 2 | 100 | 0.99
R22 | ~ | DNP |  |  |  |  | 1 | 2
R23,R24 | 4k7 |  | CRCW04024K70FKED | Panasonic Industry | 541-4.70KLCT-ND | Digikey | 2 | 3 | 100 | 1.57
R25 | 14k7 |  | ERA-2APB1472X | Panasonic Industry | P17731CT-ND | Digikey | 1 | 2 | 10 | 4.5199999999999996
R26 | 4k7 |  | ERA-2ARB472X | Panasonic Industry | P4.7KCPCT-ND | Digikey | 1 | 2 | 10 | 4.99
R27,R28,R29,R30,R31,R32 | 4k7 | DNP | CRCW04024K70FKED | Vishay Dale | 541-4.70KLCT-ND | Digikey | 6 | 7
TP1,TP3 | 5000 |  | 5000 | Keystone | 36-5000-ND | Digikey | 2 | 3 | 10 | 2.04
TP2 | 5001 |  | 5001 | Keystone | 36-5001-ND | Digikey | 1 | 2 | 10 | 2.0299999999999998
TP4,TP5,TP6,TP7,TP8,TP9 | 5015 |  | 5015 | Keystone | 36-5015CT-ND | Digikey | 6 | 7 | 25 | 8.2899999999999991
U1,U8,U11,U14,U17,U20 | LTC2945IUD-1 |  | LTC2945IUD#TRPBF | Analog Devices Inc. | LTC2945IUD#TRPBFDKR-ND | Digikey | 6 | 7 | 10 | 110.97
U2,U3,U9,U10,U12,U13,U15,U16,U18,U19,U21,U22 | ACPL-064L |  | ACPL-064L-500E | Broadcom Limited | 516-2614-6-ND | Digikey | 12 | 14 | 15 | 56.265000000000001
U4 | TPS62912 |  | TPS62912RPUR | Texas Instruments | 595-TPS62912RPUR | Mouser | 1 | 2 | 3 | 7.77
U5,U6 | TCA9803 |  | TCA9803DGKR | Texas Instruments | 296-47829-6-ND | Digikey | 2 | 3 | 10 | 6.84
U7 | P82715DR |  | P82B715DR | Texas Instruments | 296-24729-6-ND | Digikey | 1 | 2 | 5 | 13.55
 |  |  |  |  |  |  |  |  | TOTAL COST: | 302.25499999999994
